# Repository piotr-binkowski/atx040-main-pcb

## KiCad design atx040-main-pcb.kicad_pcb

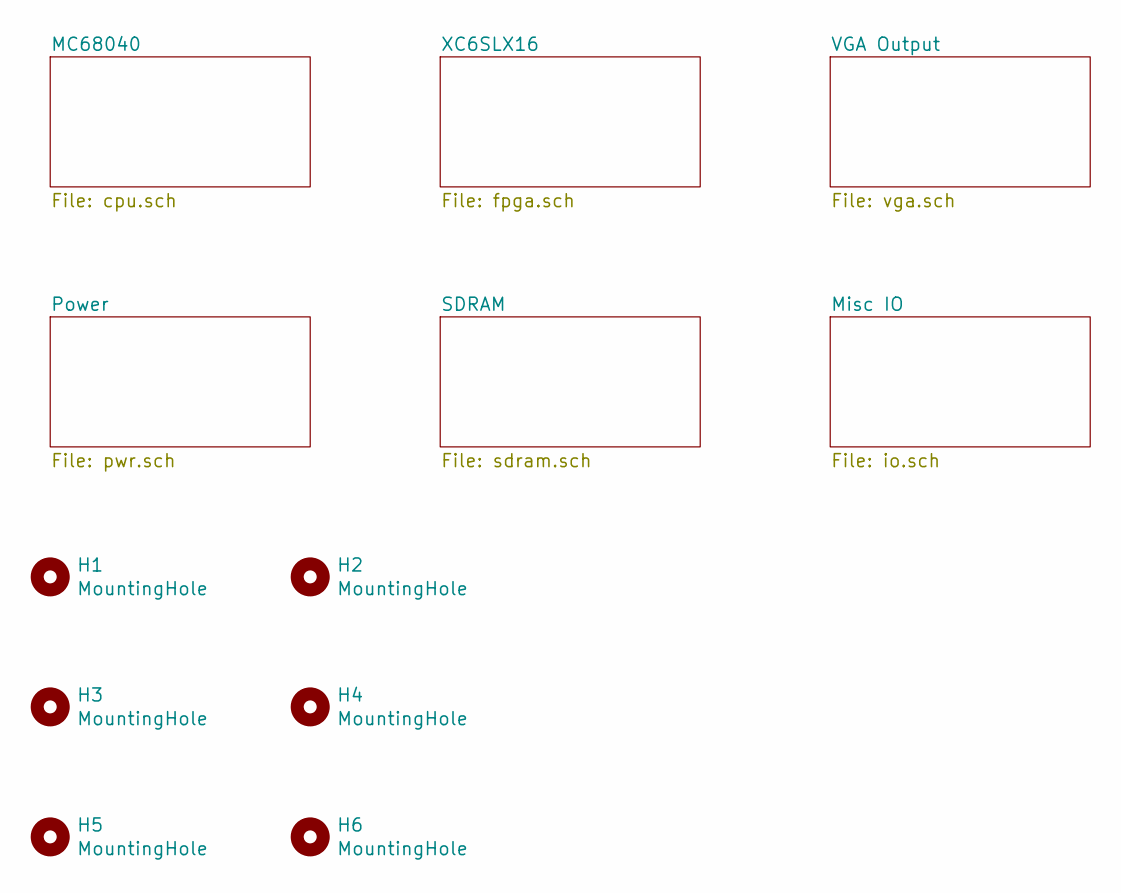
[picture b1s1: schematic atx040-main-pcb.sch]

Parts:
H1, H2, H3, H4, H5, H6: MountingHole; MountingHole_3.7mm_Pad_Via

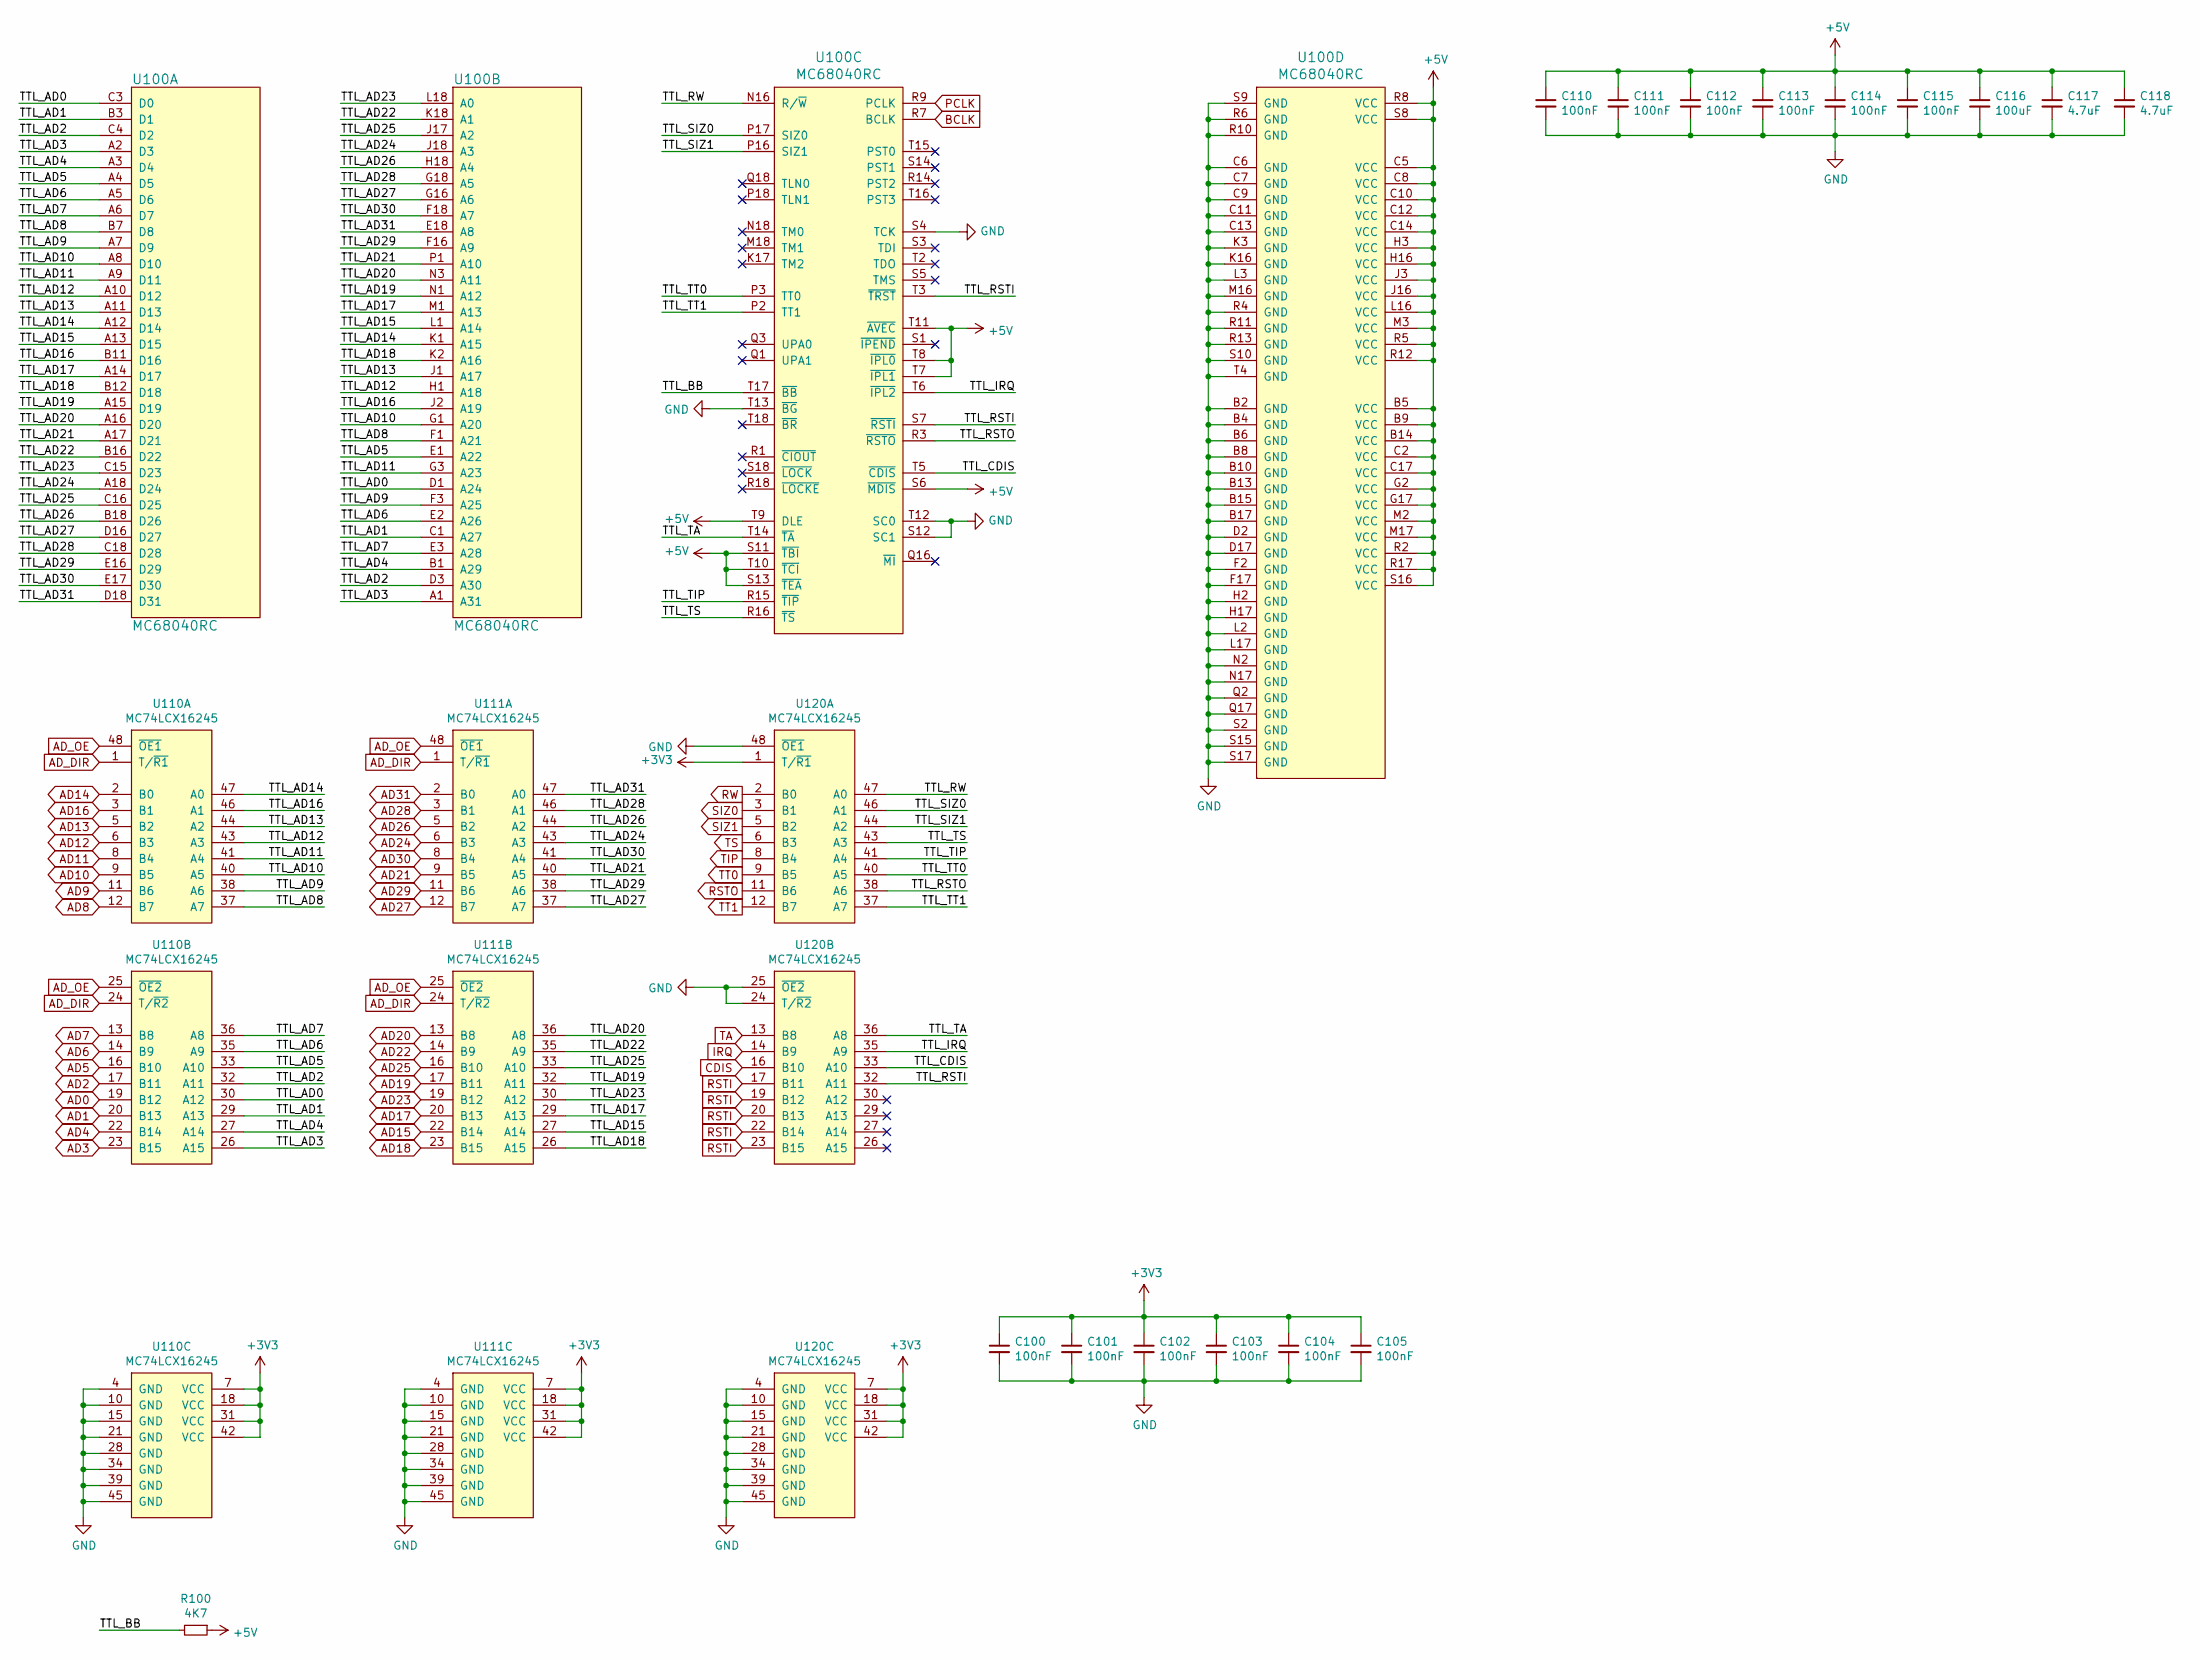
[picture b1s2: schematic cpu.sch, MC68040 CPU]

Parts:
C100, C101, C102, C103, C104, C105, C110, C111, C112, C113, C114, C115: 100nF; C_0603_1608Metric
C116: 100uF; C_1206_3216Metric
C117, C118: 4.7uF; C_0805_2012Metric
R100: 4K7; R_0603_1608Metric
U100: MC68040RC; PGA179
U110, U111, U120: MC74LCX16245; TSSOP-48_6.1x12.5mm_P0.5mm; LCSC C233495

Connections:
+3V3: C100.1, C101.1, C102.1, C103.1, C104.1, C105.1, U110.7 (VCC), U110.18 (VCC), U110.31 (VCC), U110.42 (VCC), U111.7 (VCC), U111.18 (VCC), U111.31 (VCC), U111.42 (VCC), U120.1 (T/~R1), U120.7 (VCC), U120.18 (VCC), U120.31 (VCC), U120.42 (VCC); also elsewhere on the board
+5V: C110.1, C111.1, C112.1, C113.1, C114.1, C115.1, C116.1, C117.1, C118.1, R100.1, U100.B5 (VCC), U100.B9 (VCC), U100.B14 (VCC), U100.C2 (VCC), U100.C5 (VCC), U100.C8 (VCC), U100.C10 (VCC), U100.C12 (VCC), U100.C14 (VCC), U100.C17 (VCC), U100.G2 (VCC), U100.G17 (VCC), U100.H3 (VCC), U100.H16 (VCC), U100.J3 (VCC), U100.J16 (VCC), U100.L16 (VCC), U100.M2 (VCC), U100.M3 (VCC), U100.M17 (VCC), U100.R2 (VCC), U100.R5 (VCC), U100.R8 (VCC), U100.R12 (VCC), U100.R17 (VCC), U100.S6 (~MDIS), U100.S8 (VCC), U100.S11 (~TBI), U100.S13 (~TEA), U100.S16 (VCC), U100.T7 (~IPL1), U100.T8 (~IPL0), U100.T9 (DLE), U100.T10 (~TCI), U100.T11 (~AVEC); also elsewhere on the board
/MC68040/TTL_AD0: U100.C3 (D0), U100.D1 (A24), U110.30 (A12)
/MC68040/TTL_AD1: U100.B3 (D1), U100.C1 (A27), U110.29 (A13)
/MC68040/TTL_AD2: U100.C4 (D2), U100.D3 (A30), U110.32 (A11)
/MC68040/TTL_AD3: U100.A1 (A31), U100.A2 (D3), U110.26 (A15)
/MC68040/TTL_AD4: U100.A3 (D4), U100.B1 (A29), U110.27 (A14)
/MC68040/TTL_AD5: U100.A4 (D5), U100.E1 (A22), U110.33 (A10)
/MC68040/TTL_AD6: U100.A5 (D6), U100.E2 (A26), U110.35 (A9)
/MC68040/TTL_AD7: U100.A6 (D7), U100.E3 (A28), U110.36 (A8)
/MC68040/TTL_AD8: U100.B7 (D8), U100.F1 (A21), U110.37 (A7)
/MC68040/TTL_AD9: U100.A7 (D9), U100.F3 (A25), U110.38 (A6)
/MC68040/TTL_AD10: U100.A8 (D10), U100.G1 (A20), U110.40 (A5)
/MC68040/TTL_AD11: U100.A9 (D11), U100.G3 (A23), U110.41 (A4)
/MC68040/TTL_AD12: U100.A10 (D12), U100.H1 (A18), U110.43 (A3)
/MC68040/TTL_AD13: U100.A11 (D13), U100.J1 (A17), U110.44 (A2)
/MC68040/TTL_AD14: U100.A12 (D14), U100.K1 (A15), U110.47 (A0)
/MC68040/TTL_AD15: U100.A13 (D15), U100.L1 (A14), U111.27 (A14)
/MC68040/TTL_AD16: U100.B11 (D16), U100.J2 (A19), U110.46 (A1)
/MC68040/TTL_AD17: U100.A14 (D17), U100.M1 (A13), U111.29 (A13)
/MC68040/TTL_AD18: U100.B12 (D18), U100.K2 (A16), U111.26 (A15)
/MC68040/TTL_AD19: U100.A15 (D19), U100.N1 (A12), U111.32 (A11)
/MC68040/TTL_AD20: U100.A16 (D20), U100.N3 (A11), U111.36 (A8)
/MC68040/TTL_AD21: U100.A17 (D21), U100.P1 (A10), U111.40 (A5)
/MC68040/TTL_AD22: U100.B16 (D22), U100.K18 (A1), U111.35 (A9)
/MC68040/TTL_AD23: U100.C15 (D23), U100.L18 (A0), U111.30 (A12)
/MC68040/TTL_AD24: U100.A18 (D24), U100.J18 (A3), U111.43 (A3)
/MC68040/TTL_AD25: U100.C16 (D25), U100.J17 (A2), U111.33 (A10)
/MC68040/TTL_AD26: U100.B18 (D26), U100.H18 (A4), U111.44 (A2)
/MC68040/TTL_AD27: U100.D16 (D27), U100.G16 (A6), U111.37 (A7)
/MC68040/TTL_AD28: U100.C18 (D28), U100.G18 (A5), U111.46 (A1)
/MC68040/TTL_AD29: U100.E16 (D29), U100.F16 (A9), U111.38 (A6)
/MC68040/TTL_AD30: U100.E17 (D30), U100.F18 (A7), U111.41 (A4)
/MC68040/TTL_AD31: U100.D18 (D31), U100.E18 (A8), U111.47 (A0)
/MC68040/TTL_BB: R100.2, U100.T17 (~BB)
/MC68040/TTL_CDIS: U100.T5 (~CDIS), U120.33 (A10)
/MC68040/TTL_IRQ: U100.T6 (~IPL2), U120.35 (A9)
/MC68040/TTL_RSTI: U100.S7 (~RSTI), U100.T3 (~TRST), U120.32 (A11)
/MC68040/TTL_RSTO: U100.R3 (~RSTO), U120.38 (A6)
/MC68040/TTL_RW: U100.N16 (R/~W), U120.47 (A0)
/MC68040/TTL_SIZ0: U100.P17 (SIZ0), U120.46 (A1)
/MC68040/TTL_SIZ1: U100.P16 (SIZ1), U120.44 (A2)
/MC68040/TTL_TA: U100.T14 (~TA), U120.36 (A8)
/MC68040/TTL_TIP: U100.R15 (~TIP), U120.41 (A4)
/MC68040/TTL_TS: U100.R16 (~TS), U120.43 (A3)
/MC68040/TTL_TT0: U100.P3 (TT0), U120.40 (A5)
/MC68040/TTL_TT1: U100.P2 (TT1), U120.37 (A7)
AD0: U110.19 (B12); also elsewhere on the board
AD1: U110.20 (B13); also elsewhere on the board
AD2: U110.17 (B11); also elsewhere on the board
AD3: U110.23 (B15); also elsewhere on the board
AD4: U110.22 (B14); also elsewhere on the board
AD5: U110.16 (B10); also elsewhere on the board
AD6: U110.14 (B9); also elsewhere on the board
AD7: U110.13 (B8); also elsewhere on the board
AD8: U110.12 (B7); also elsewhere on the board
AD9: U110.11 (B6); also elsewhere on the board
AD10: U110.9 (B5); also elsewhere on the board
AD11: U110.8 (B4); also elsewhere on the board
AD12: U110.6 (B3); also elsewhere on the board
AD13: U110.5 (B2); also elsewhere on the board
AD14: U110.2 (B0); also elsewhere on the board
AD15: U111.22 (B14); also elsewhere on the board
AD16: U110.3 (B1); also elsewhere on the board
AD17: U111.20 (B13); also elsewhere on the board
AD18: U111.23 (B15); also elsewhere on the board
AD19: U111.17 (B11); also elsewhere on the board
AD20: U111.13 (B8); also elsewhere on the board
AD21: U111.9 (B5); also elsewhere on the board
AD22: U111.14 (B9); also elsewhere on the board
AD23: U111.19 (B12); also elsewhere on the board
AD24: U111.6 (B3); also elsewhere on the board
AD25: U111.16 (B10); also elsewhere on the board
AD26: U111.5 (B2); also elsewhere on the board
AD27: U111.12 (B7); also elsewhere on the board
AD28: U111.3 (B1); also elsewhere on the board
AD29: U111.11 (B6); also elsewhere on the board
AD30: U111.8 (B4); also elsewhere on the board
AD31: U111.2 (B0); also elsewhere on the board
AD_DIR: U110.1 (T/~R1), U110.24 (T/~R2), U111.1 (T/~R1), U111.24 (T/~R2); also elsewhere on the board
AD_OE: U110.25 (~OE2), U110.48 (~OE1), U111.25 (~OE2), U111.48 (~OE1); also elsewhere on the board
BCLK: U100.R7 (BCLK); also elsewhere on the board
CDIS: U120.16 (B10); also elsewhere on the board
GND: C100.2, C101.2, C102.2, C103.2, C104.2, C105.2, C110.2, C111.2, C112.2, C113.2, C114.2, C115.2, C116.2, C117.2, C118.2, U100.B2 (GND), U100.B4 (GND), U100.B6 (GND), U100.B8 (GND), U100.B10 (GND), U100.B13 (GND), U100.B15 (GND), U100.B17 (GND), U100.C6 (GND), U100.C7 (GND), U100.C9 (GND), U100.C11 (GND), U100.C13 (GND), U100.D2 (GND), U100.D17 (GND), U100.F2 (GND), U100.F17 (GND), U100.H2 (GND), U100.H17 (GND), U100.K3 (GND), U100.K16 (GND), U100.L2 (GND), U100.L3 (GND), U100.L17 (GND), U100.M16 (GND), U100.N2 (GND), U100.N17 (GND), U100.Q2 (GND), U100.Q17 (GND), U100.R4 (GND), U100.R6 (GND), U100.R10 (GND), U100.R11 (GND), U100.R13 (GND), U100.S2 (GND), U100.S4 (TCK), U100.S9 (GND), U100.S10 (GND), U100.S12 (SC1), U100.S15 (GND), U100.S17 (GND), U100.T4 (GND), U100.T12 (SC0), U100.T13 (~BG), U110.4 (GND), U110.10 (GND), U110.15 (GND), U110.21 (GND), U110.28 (GND), U110.34 (GND), U110.39 (GND), U110.45 (GND), U111.4 (GND), U111.10 (GND), U111.15 (GND), U111.21 (GND), U111.28 (GND), U111.34 (GND), U111.39 (GND), U111.45 (GND), U120.4 (GND), U120.10 (GND), U120.15 (GND), U120.21 (GND), U120.24 (T/~R2), U120.25 (~OE2), U120.28 (GND), U120.34 (GND), U120.39 (GND), U120.45 (GND), U120.48 (~OE1); also elsewhere on the board
IRQ: U120.14 (B9); also elsewhere on the board
PCLK: U100.R9 (PCLK); also elsewhere on the board
RSTI: U120.17 (B11), U120.19 (B12), U120.20 (B13), U120.22 (B14), U120.23 (B15); also elsewhere on the board
RSTO: U120.11 (B6); also elsewhere on the board
RW: U120.2 (B0); also elsewhere on the board
SIZ0: U120.3 (B1); also elsewhere on the board
SIZ1: U120.5 (B2); also elsewhere on the board
TA: U120.13 (B8); also elsewhere on the board
TIP: U120.8 (B4); also elsewhere on the board
TS: U120.6 (B3); also elsewhere on the board
TT0: U120.9 (B5); also elsewhere on the board
TT1: U120.12 (B7); also elsewhere on the board

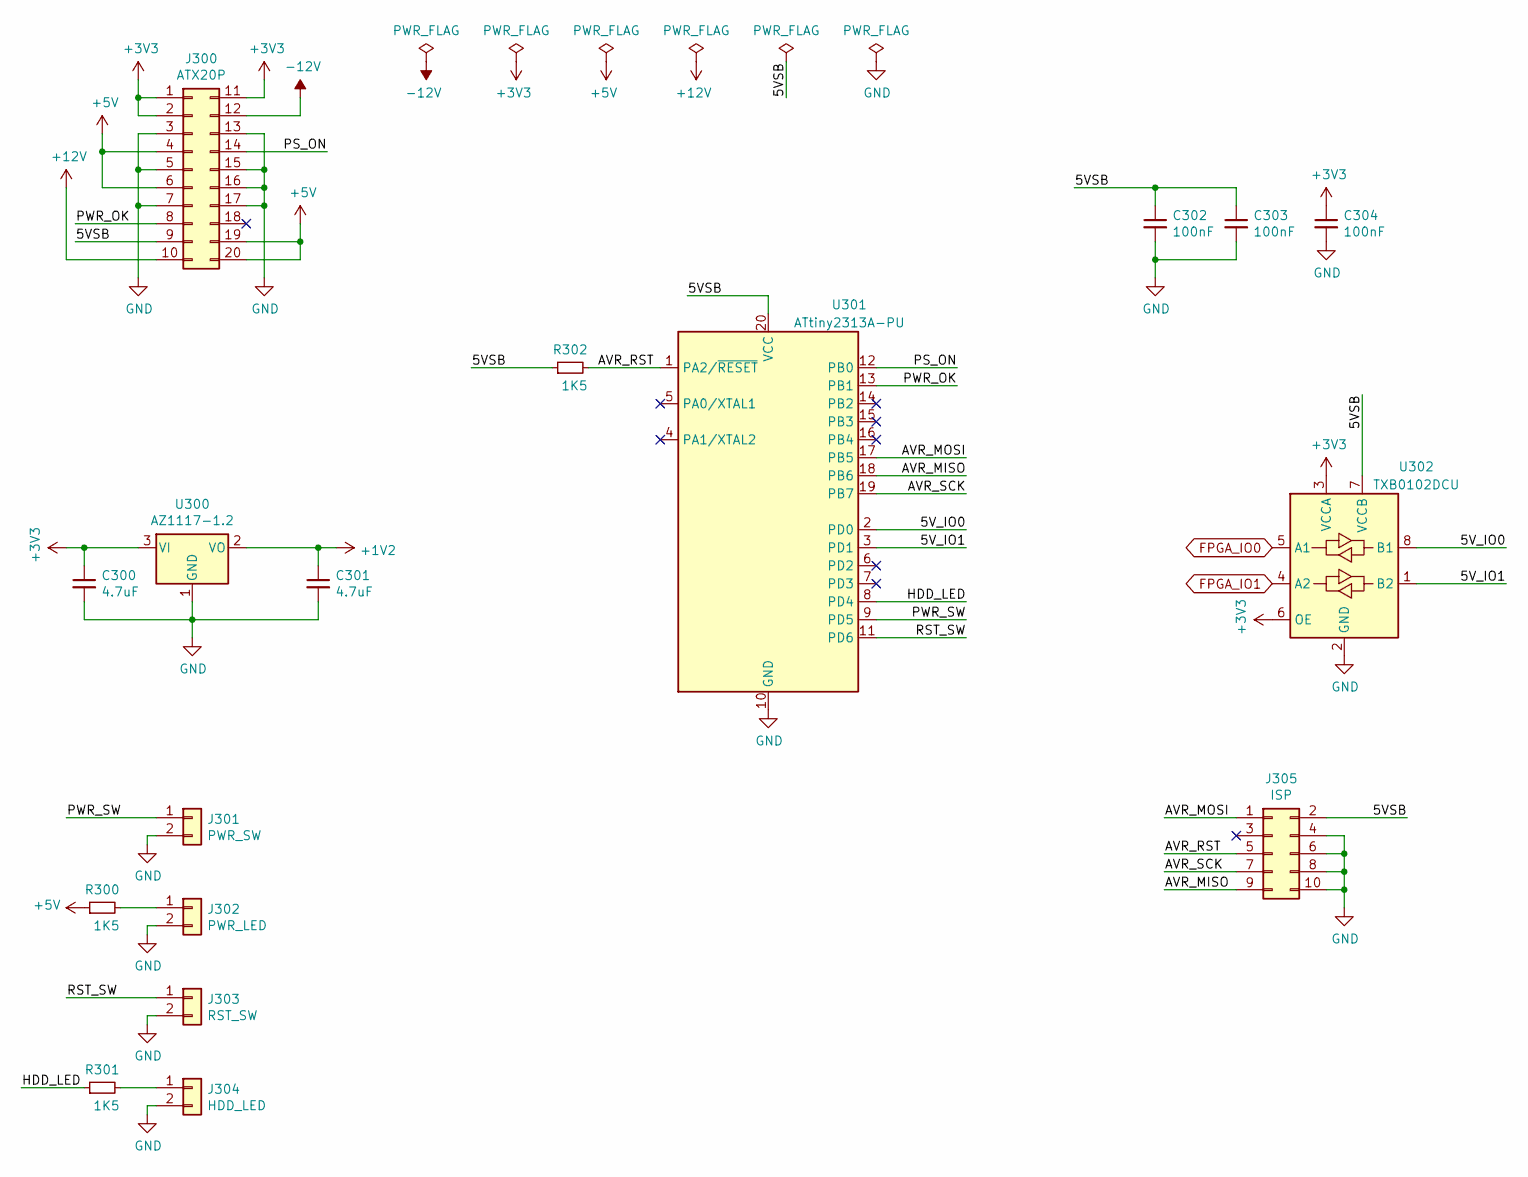
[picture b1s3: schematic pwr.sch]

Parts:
C300, C301: 4.7uF; C_0805_2012Metric
C302, C303, C304: 100nF; C_0603_1608Metric
J300: ATX20P; Molex_Mini-Fit_Jr_5566-20A_2x10_P4.20mm_Vertical
J301: PWR_SW; PinHeader_1x02_P2.54mm_Vertical
J302: PWR_LED; PinHeader_1x02_P2.54mm_Vertical
J303: RST_SW; PinHeader_1x02_P2.54mm_Vertical
J304: HDD_LED; PinHeader_1x02_P2.54mm_Vertical
J305: ISP; PinHeader_2x05_P2.54mm_Vertical
R300, R301, R302: 1K5; R_0603_1608Metric
U300: AZ1117-1.2; TO-252-2; LCSC C441832
U301: ATtiny2313A-PU; DIP-20_W7.62mm
U302: TXB0102DCU; VSSOP-8_2.4x2.1mm_P0.5mm; LCSC C60709

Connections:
+1V2: C301.1, U300.2 (VO); also elsewhere on the board
+3V3: C300.1, C304.1, J300.1, J300.2, J300.11, U300.3 (VI), U302.3 (VCCA), U302.6 (OE); also elsewhere on the board
+5V: J300.4, J300.6, J300.19, J300.20, R300.1; also elsewhere on the board
+12V: J300.10; also elsewhere on the board
-12V: J300.12
/Power/5VSB: C302.1, C303.1, J300.9, J305.2, R302.1, U301.20 (VCC), U302.7 (VCCB)
/Power/5V_IO0: U301.2 (PD0), U302.8 (B1)
/Power/5V_IO1: U301.3 (PD1), U302.1 (B2)
/Power/AVR_MISO: J305.9, U301.18 (PB6)
/Power/AVR_MOSI: J305.1, U301.17 (PB5)
/Power/AVR_RST: J305.5, R302.2, U301.1 (PA2/~RESET)
/Power/AVR_SCK: J305.7, U301.19 (PB7)
/Power/HDD_LED: R301.1, U301.8 (PD4)
/Power/PS_ON: J300.14, U301.12 (PB0)
/Power/PWR_OK: J300.8, U301.13 (PB1)
/Power/PWR_SW: J301.1, U301.9 (PD5)
/Power/RST_SW: J303.1, U301.11 (PD6)
FPGA_IO0: U302.5 (A1); also elsewhere on the board
FPGA_IO1: U302.4 (A2); also elsewhere on the board
GND: C300.2, C301.2, C302.2, C303.2, C304.2, J300.3, J300.5, J300.7, J300.13, J300.15, J300.16, J300.17, J301.2, J302.2, J303.2, J304.2, J305.4, J305.6, J305.8, J305.10, U300.1 (GND), U301.10 (GND), U302.2 (GND); also elsewhere on the board
unnamed: J302.1, R300.2
unnamed: J304.1, R301.2

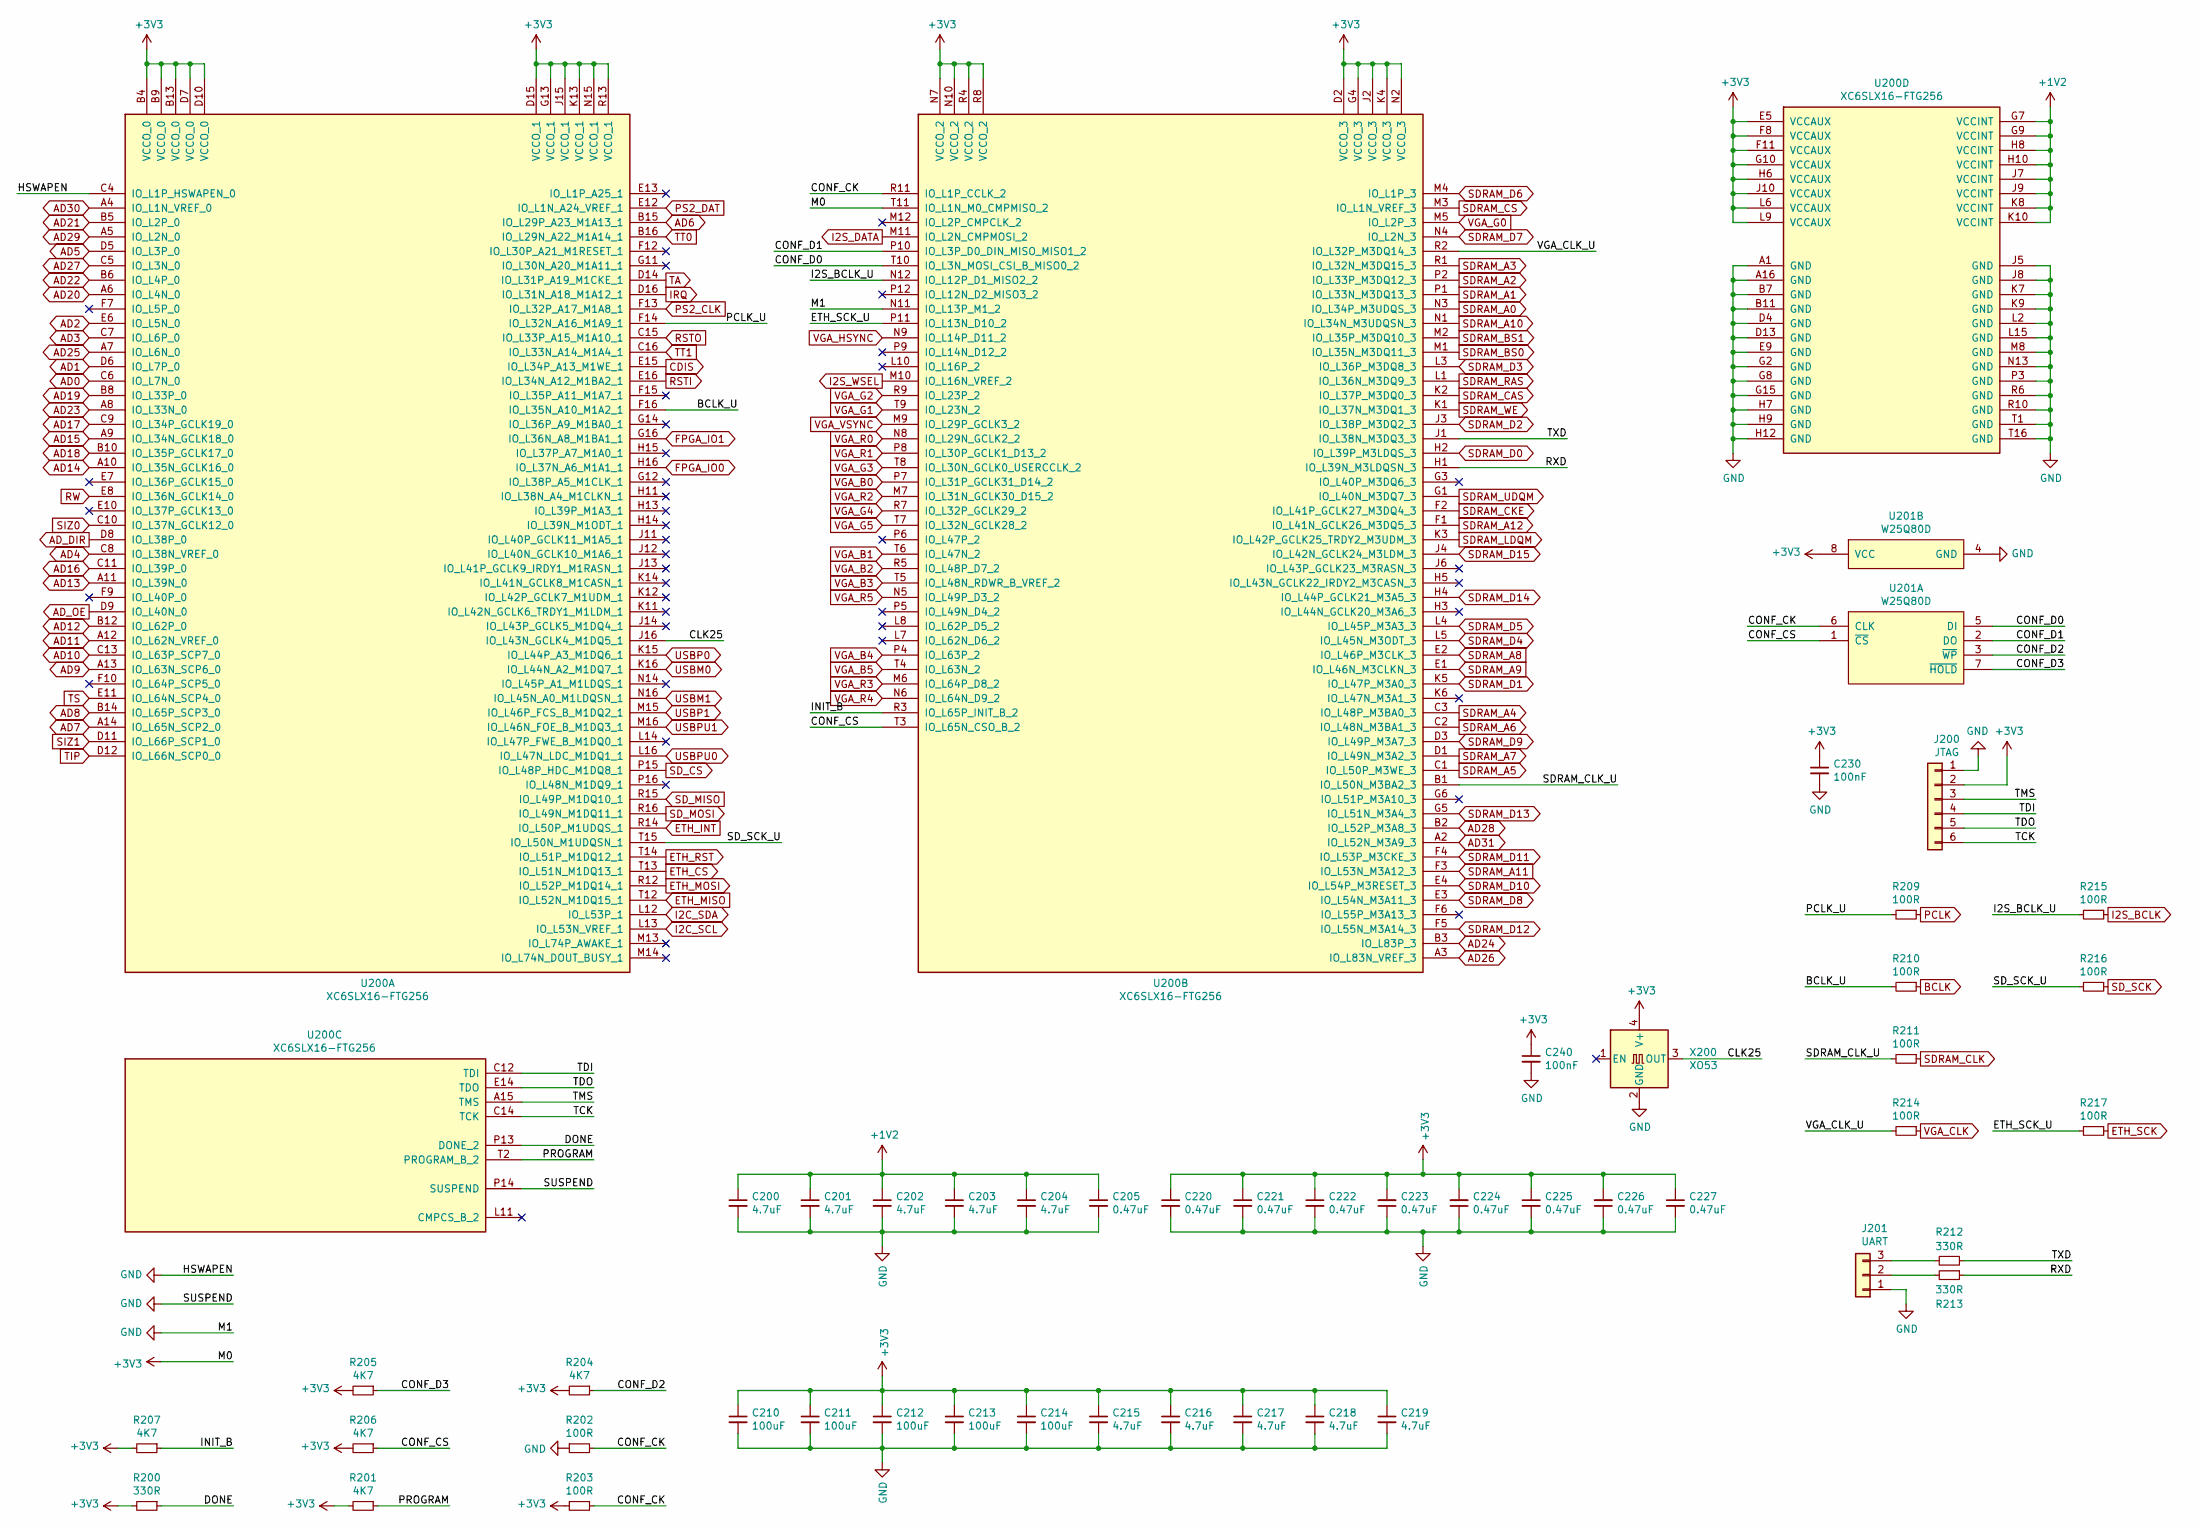
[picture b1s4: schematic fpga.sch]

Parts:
C200, C201, C202, C203, C204, C215, C216, C217, C218, C219: 4.7uF; C_0805_2012Metric
C205, C220, C221, C222, C223, C224, C225, C226, C227: 0.47uF; C_0402_1005Metric
C210, C211, C212, C213, C214: 100uF; C_1206_3216Metric
C230, C240: 100nF; C_0402_1005Metric
J200: JTAG; PinHeader_1x06_P2.54mm_Vertical
J201: UART; PinHeader_1x03_P2.54mm_Vertical
R200: 330R; R_0603_1608Metric
R201, R204, R205, R206, R207: 4K7; R_0603_1608Metric
R202, R203: 100R; R_0603_1608Metric
R209, R210, R211, R214, R215, R216, R217: 100R; R_0402_1005Metric
R212, R213: 330R; R_0402_1005Metric
U200: XC6SLX16-FTG256; Xilinx_FTG256
U201: W25Q80D; SOIC-8_3.9x4.9mm_P1.27mm
X200: XO53; Oscillator_SMD_EuroQuartz_XO53-4Pin_5.0x3.2mm; LCSC C18170

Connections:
+1V2: C200.1, C201.1, C202.1, C203.1, C204.1, C205.1, U200.G7 (VCCINT), U200.G9 (VCCINT), U200.H8 (VCCINT), U200.H10 (VCCINT), U200.J7 (VCCINT), U200.J9 (VCCINT), U200.K8 (VCCINT), U200.K10 (VCCINT); also elsewhere on the board
+3V3: C210.1, C211.1, C212.1, C213.1, C214.1, C215.1, C216.1, C217.1, C218.1, C219.1, C220.1, C221.1, C222.1, C223.2, C224.2, C225.1, C226.2, C227.1, C230.1, C240.1, J200.2, R200.2, R201.2, R203.2, R204.2, R205.2, R206.2, R207.2, U200.B4 (VCCO_0), U200.B9 (VCCO_0), U200.B13 (VCCO_0), U200.D2 (VCCO_3), U200.D7 (VCCO_0), U200.D10 (VCCO_0), U200.D15 (VCCO_1), U200.E5 (VCCAUX), U200.F8 (VCCAUX), U200.F11 (VCCAUX), U200.G4 (VCCO_3), U200.G10 (VCCAUX), U200.G13 (VCCO_1), U200.H6 (VCCAUX), U200.J2 (VCCO_3), U200.J10 (VCCAUX), U200.J15 (VCCO_1), U200.K4 (VCCO_3), U200.K13 (VCCO_1), U200.L6 (VCCAUX), U200.L9 (VCCAUX), U200.N2 (VCCO_3), U200.N7 (VCCO_2), U200.N10 (VCCO_2), U200.N15 (VCCO_1), U200.R4 (VCCO_2), U200.R8 (VCCO_2), U200.R13 (VCCO_1), U200.T11 (IO_L1N_M0_CMPMISO_2), U201.8 (VCC), X200.4 (V+); also elsewhere on the board
/XC6SLX16/BCLK_U: R210.2, U200.F16 (IO_L35N_A10_M1A2_1)
/XC6SLX16/CLK25: U200.J16 (IO_L43N_GCLK4_M1DQ5_1), X200.3 (OUT)
/XC6SLX16/CONF_CK: R202.2, R203.1, U200.R11 (IO_L1P_CCLK_2), U201.6 (CLK)
/XC6SLX16/CONF_CS: R206.1, U200.T3 (IO_L65N_CSO_B_2), U201.1 (~CS)
/XC6SLX16/CONF_D0: U200.T10 (IO_L3N_MOSI_CSI_B_MISO0_2), U201.5 (DI)
/XC6SLX16/CONF_D1: U200.P10 (IO_L3P_D0_DIN_MISO_MISO1_2), U201.2 (DO)
/XC6SLX16/CONF_D2: R204.1, U201.3 (~WP)
/XC6SLX16/CONF_D3: R205.1, U201.7 (~HOLD)
/XC6SLX16/DONE: R200.1, U200.P13 (DONE_2)
/XC6SLX16/ETH_SCK_U: R217.2, U200.P11 (IO_L13N_D10_2)
/XC6SLX16/I2S_BCLK_U: R215.2, U200.N12 (IO_L12P_D1_MISO2_2)
/XC6SLX16/INIT_B: R207.1, U200.R3 (IO_L65P_INIT_B_2)
/XC6SLX16/PCLK_U: R209.2, U200.F14 (IO_L32N_A16_M1A9_1)
/XC6SLX16/PROGRAM: R201.1, U200.T2 (PROGRAM_B_2)
/XC6SLX16/RXD: R213.1, U200.H1 (IO_L39N_M3LDQSN_3)
/XC6SLX16/SDRAM_CLK_U: R211.2, U200.B1 (IO_L50N_M3BA2_3)
/XC6SLX16/SD_SCK_U: R216.2, U200.T15 (IO_L50N_M1UDQSN_1)
/XC6SLX16/TCK: J200.6, U200.C14 (TCK)
/XC6SLX16/TDI: J200.4, U200.C12 (TDI)
/XC6SLX16/TDO: J200.5, U200.E14 (TDO)
/XC6SLX16/TMS: J200.3, U200.A15 (TMS)
/XC6SLX16/TXD: R212.1, U200.J1 (IO_L38N_M3DQ3_3)
/XC6SLX16/VGA_CLK_U: R214.2, U200.R2 (IO_L32P_M3DQ14_3)
AD0: U200.C6 (IO_L7N_0); also elsewhere on the board
AD1: U200.D6 (IO_L7P_0); also elsewhere on the board
AD2: U200.E6 (IO_L5N_0); also elsewhere on the board
AD3: U200.C7 (IO_L6P_0); also elsewhere on the board
AD4: U200.C8 (IO_L38N_VREF_0); also elsewhere on the board
AD5: U200.D5 (IO_L3P_0); also elsewhere on the board
AD6: U200.B15 (IO_L29P_A23_M1A13_1); also elsewhere on the board
AD7: U200.A14 (IO_L65N_SCP2_0); also elsewhere on the board
AD8: U200.B14 (IO_L65P_SCP3_0); also elsewhere on the board
AD9: U200.A13 (IO_L63N_SCP6_0); also elsewhere on the board
AD10: U200.C13 (IO_L63P_SCP7_0); also elsewhere on the board
AD11: U200.A12 (IO_L62N_VREF_0); also elsewhere on the board
AD12: U200.B12 (IO_L62P_0); also elsewhere on the board
AD13: U200.A11 (IO_L39N_0); also elsewhere on the board
AD14: U200.A10 (IO_L35N_GCLK16_0); also elsewhere on the board
AD15: U200.A9 (IO_L34N_GCLK18_0); also elsewhere on the board
AD16: U200.C11 (IO_L39P_0); also elsewhere on the board
AD17: U200.C9 (IO_L34P_GCLK19_0); also elsewhere on the board
AD18: U200.B10 (IO_L35P_GCLK17_0); also elsewhere on the board
AD19: U200.B8 (IO_L33P_0); also elsewhere on the board
AD20: U200.A6 (IO_L4N_0); also elsewhere on the board
AD21: U200.B5 (IO_L2P_0); also elsewhere on the board
AD22: U200.B6 (IO_L4P_0); also elsewhere on the board
AD23: U200.A8 (IO_L33N_0); also elsewhere on the board
AD24: U200.B3 (IO_L83P_3); also elsewhere on the board
AD25: U200.A7 (IO_L6N_0); also elsewhere on the board
AD26: U200.A3 (IO_L83N_VREF_3); also elsewhere on the board
AD27: U200.C5 (IO_L3N_0); also elsewhere on the board
AD28: U200.B2 (IO_L52P_M3A8_3); also elsewhere on the board
AD29: U200.A5 (IO_L2N_0); also elsewhere on the board
AD30: U200.A4 (IO_L1N_VREF_0); also elsewhere on the board
AD31: U200.A2 (IO_L52N_M3A9_3); also elsewhere on the board
AD_DIR: U200.D8 (IO_L38P_0); also elsewhere on the board
AD_OE: U200.D9 (IO_L40N_0); also elsewhere on the board
BCLK: R210.1; also elsewhere on the board
CDIS: U200.E15 (IO_L34P_A13_M1WE_1); also elsewhere on the board
ETH_CS: U200.T13 (IO_L51N_M1DQ13_1); also elsewhere on the board
ETH_INT: U200.R14 (IO_L50P_M1UDQS_1); also elsewhere on the board
ETH_MISO: U200.T12 (IO_L52N_M1DQ15_1); also elsewhere on the board
ETH_MOSI: U200.R12 (IO_L52P_M1DQ14_1); also elsewhere on the board
ETH_RST: U200.T14 (IO_L51P_M1DQ12_1); also elsewhere on the board
ETH_SCK: R217.1; also elsewhere on the board
FPGA_IO0: U200.H16 (IO_L37N_A6_M1A1_1); also elsewhere on the board
FPGA_IO1: U200.G16 (IO_L36N_A8_M1BA1_1); also elsewhere on the board
GND: C200.2, C201.2, C202.2, C203.2, C204.2, C205.2, C210.2, C211.2, C212.2, C213.2, C214.2, C215.2, C216.2, C217.2, C218.2, C219.2, C220.2, C221.2, C222.2, C223.1, C224.1, C225.2, C226.1, C227.2, C230.2, C240.2, J200.1, J201.1, R202.1, U200.A1 (GND), U200.A16 (GND), U200.B7 (GND), U200.B11 (GND), U200.C4 (IO_L1P_HSWAPEN_0), U200.D4 (GND), U200.D13 (GND), U200.E9 (GND), U200.G2 (GND), U200.G8 (GND), U200.G15 (GND), U200.H7 (GND), U200.H9 (GND), U200.H12 (GND), U200.J5 (GND), U200.J8 (GND), U200.K7 (GND), U200.K9 (GND), U200.L2 (GND), U200.L15 (GND), U200.M8 (GND), U200.N11 (IO_L13P_M1_2), U200.N13 (GND), U200.P3 (GND), U200.P14 (SUSPEND), U200.R6 (GND), U200.R10 (GND), U200.T1 (GND), U200.T16 (GND), U201.4 (GND), X200.2 (GND); also elsewhere on the board
I2C_SCL: U200.L13 (IO_L53N_VREF_1); also elsewhere on the board
I2C_SDA: U200.L12 (IO_L53P_1); also elsewhere on the board
I2S_BCLK: R215.1; also elsewhere on the board
I2S_DATA: U200.M11 (IO_L2N_CMPMOSI_2); also elsewhere on the board
I2S_WSEL: U200.M10 (IO_L16N_VREF_2); also elsewhere on the board
IRQ: U200.D16 (IO_L31N_A18_M1A12_1); also elsewhere on the board
unnamed: J201.2, R213.2
unnamed: J201.3, R212.2
PCLK: R209.1; also elsewhere on the board
PS2_CLK: U200.F13 (IO_L32P_A17_M1A8_1); also elsewhere on the board
PS2_DAT: U200.E12 (IO_L1N_A24_VREF_1); also elsewhere on the board
RSTI: U200.E16 (IO_L34N_A12_M1BA2_1); also elsewhere on the board
RSTO: U200.C15 (IO_L33P_A15_M1A10_1); also elsewhere on the board
RW: U200.E8 (IO_L36N_GCLK14_0); also elsewhere on the board
SDRAM_A0: U200.N3 (IO_L34P_M3UDQS_3); also elsewhere on the board
SDRAM_A1: U200.P1 (IO_L33N_M3DQ13_3); also elsewhere on the board
SDRAM_A2: U200.P2 (IO_L33P_M3DQ12_3); also elsewhere on the board
SDRAM_A3: U200.R1 (IO_L32N_M3DQ15_3); also elsewhere on the board
SDRAM_A4: U200.C3 (IO_L48P_M3BA0_3); also elsewhere on the board
SDRAM_A5: U200.C1 (IO_L50P_M3WE_3); also elsewhere on the board
SDRAM_A6: U200.C2 (IO_L48N_M3BA1_3); also elsewhere on the board
SDRAM_A7: U200.D1 (IO_L49N_M3A2_3); also elsewhere on the board
SDRAM_A8: U200.E2 (IO_L46P_M3CLK_3); also elsewhere on the board
SDRAM_A9: U200.E1 (IO_L46N_M3CLKN_3); also elsewhere on the board
SDRAM_A10: U200.N1 (IO_L34N_M3UDQSN_3); also elsewhere on the board
SDRAM_A11: U200.F3 (IO_L53N_M3A12_3); also elsewhere on the board
SDRAM_A12: U200.F1 (IO_L41N_GCLK26_M3DQ5_3); also elsewhere on the board
SDRAM_BS0: U200.M1 (IO_L35N_M3DQ11_3); also elsewhere on the board
SDRAM_BS1: U200.M2 (IO_L35P_M3DQ10_3); also elsewhere on the board
SDRAM_CAS: U200.K2 (IO_L37P_M3DQ0_3); also elsewhere on the board
SDRAM_CKE: U200.F2 (IO_L41P_GCLK27_M3DQ4_3); also elsewhere on the board
SDRAM_CLK: R211.1; also elsewhere on the board
SDRAM_CS: U200.M3 (IO_L1N_VREF_3); also elsewhere on the board
SDRAM_D0: U200.H2 (IO_L39P_M3LDQS_3); also elsewhere on the board
SDRAM_D1: U200.K5 (IO_L47P_M3A0_3); also elsewhere on the board
SDRAM_D2: U200.J3 (IO_L38P_M3DQ2_3); also elsewhere on the board
SDRAM_D3: U200.L3 (IO_L36P_M3DQ8_3); also elsewhere on the board
SDRAM_D4: U200.L5 (IO_L45N_M3ODT_3); also elsewhere on the board
SDRAM_D5: U200.L4 (IO_L45P_M3A3_3); also elsewhere on the board
SDRAM_D6: U200.M4 (IO_L1P_3); also elsewhere on the board
SDRAM_D7: U200.N4 (IO_L2N_3); also elsewhere on the board
SDRAM_D8: U200.E3 (IO_L54N_M3A11_3); also elsewhere on the board
SDRAM_D9: U200.D3 (IO_L49P_M3A7_3); also elsewhere on the board
SDRAM_D10: U200.E4 (IO_L54P_M3RESET_3); also elsewhere on the board
SDRAM_D11: U200.F4 (IO_L53P_M3CKE_3); also elsewhere on the board
SDRAM_D12: U200.F5 (IO_L55N_M3A14_3); also elsewhere on the board
SDRAM_D13: U200.G5 (IO_L51N_M3A4_3); also elsewhere on the board
SDRAM_D14: U200.H4 (IO_L44P_GCLK21_M3A5_3); also elsewhere on the board
SDRAM_D15: U200.J4 (IO_L42N_GCLK24_M3LDM_3); also elsewhere on the board
SDRAM_LDQM: U200.K3 (IO_L42P_GCLK25_TRDY2_M3UDM_3); also elsewhere on the board
SDRAM_RAS: U200.L1 (IO_L36N_M3DQ9_3); also elsewhere on the board
SDRAM_UDQM: U200.G1 (IO_L40N_M3DQ7_3); also elsewhere on the board
SDRAM_WE: U200.K1 (IO_L37N_M3DQ1_3); also elsewhere on the board
SD_CS: U200.P15 (IO_L48P_HDC_M1DQ8_1); also elsewhere on the board
SD_MISO: U200.R15 (IO_L49P_M1DQ10_1); also elsewhere on the board
SD_MOSI: U200.R16 (IO_L49N_M1DQ11_1); also elsewhere on the board
SD_SCK: R216.1; also elsewhere on the board
SIZ0: U200.C10 (IO_L37N_GCLK12_0); also elsewhere on the board
SIZ1: U200.D11 (IO_L66P_SCP1_0); also elsewhere on the board
TA: U200.D14 (IO_L31P_A19_M1CKE_1); also elsewhere on the board
TIP: U200.D12 (IO_L66N_SCP0_0); also elsewhere on the board
TS: U200.E11 (IO_L64N_SCP4_0); also elsewhere on the board
TT0: U200.B16 (IO_L29N_A22_M1A14_1); also elsewhere on the board
TT1: U200.C16 (IO_L33N_A14_M1A4_1); also elsewhere on the board
USBM0: U200.K16 (IO_L44N_A2_M1DQ7_1); also elsewhere on the board
USBM1: U200.N16 (IO_L45N_A0_M1LDQSN_1); also elsewhere on the board
USBP0: U200.K15 (IO_L44P_A3_M1DQ6_1); also elsewhere on the board
USBP1: U200.M15 (IO_L46P_FCS_B_M1DQ2_1); also elsewhere on the board
USBPU0: U200.L16 (IO_L47N_LDC_M1DQ1_1); also elsewhere on the board
USBPU1: U200.M16 (IO_L46N_FOE_B_M1DQ3_1); also elsewhere on the board
VGA_B0: U200.P7 (IO_L31P_GCLK31_D14_2); also elsewhere on the board
VGA_B1: U200.T6 (IO_L47N_2); also elsewhere on the board
VGA_B2: U200.R5 (IO_L48P_D7_2); also elsewhere on the board
VGA_B3: U200.T5 (IO_L48N_RDWR_B_VREF_2); also elsewhere on the board
VGA_B4: U200.P4 (IO_L63P_2); also elsewhere on the board
VGA_B5: U200.T4 (IO_L63N_2); also elsewhere on the board
VGA_CLK: R214.1; also elsewhere on the board
VGA_G0: U200.M5 (IO_L2P_3); also elsewhere on the board
VGA_G1: U200.T9 (IO_L23N_2); also elsewhere on the board
VGA_G2: U200.R9 (IO_L23P_2); also elsewhere on the board
VGA_G3: U200.T8 (IO_L30N_GCLK0_USERCCLK_2); also elsewhere on the board
VGA_G4: U200.R7 (IO_L32P_GCLK29_2); also elsewhere on the board
VGA_G5: U200.T7 (IO_L32N_GCLK28_2); also elsewhere on the board
VGA_HSYNC: U200.N9 (IO_L14P_D11_2); also elsewhere on the board
VGA_R0: U200.N8 (IO_L29N_GCLK2_2); also elsewhere on the board
VGA_R1: U200.P8 (IO_L30P_GCLK1_D13_2); also elsewhere on the board
VGA_R2: U200.M7 (IO_L31N_GCLK30_D15_2); also elsewhere on the board
VGA_R3: U200.M6 (IO_L64P_D8_2); also elsewhere on the board
VGA_R4: U200.N6 (IO_L64N_D9_2); also elsewhere on the board
VGA_R5: U200.N5 (IO_L49P_D3_2); also elsewhere on the board
VGA_VSYNC: U200.M9 (IO_L29P_GCLK3_2); also elsewhere on the board
